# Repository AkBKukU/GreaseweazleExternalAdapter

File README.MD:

# Greaseweazle External Floppy Adapter

This is a simple PCB design that directly adapts a Greaseweazle floppy interface to a 25 pin (or 37 pin) external floppy drive. The idea was to allow the use of cheap external floppy drives that are missing their pass through hardware card that makes them usable in a vintage system. With the adapter you get an easy to use and robustly  cased floppy drive for use with disk image hardware.  
  
## Assembly  
Take note that the DB25 connector is put on the opposite side of the board than the power and 34 pin IDC connectors. The trace routing would have needed to be flipped to keep them all on top and this was made in a bit of a rush. It would be possible to re-route the PCB to have the connector on top, but all traces would have to cross making the routing much more complicated.

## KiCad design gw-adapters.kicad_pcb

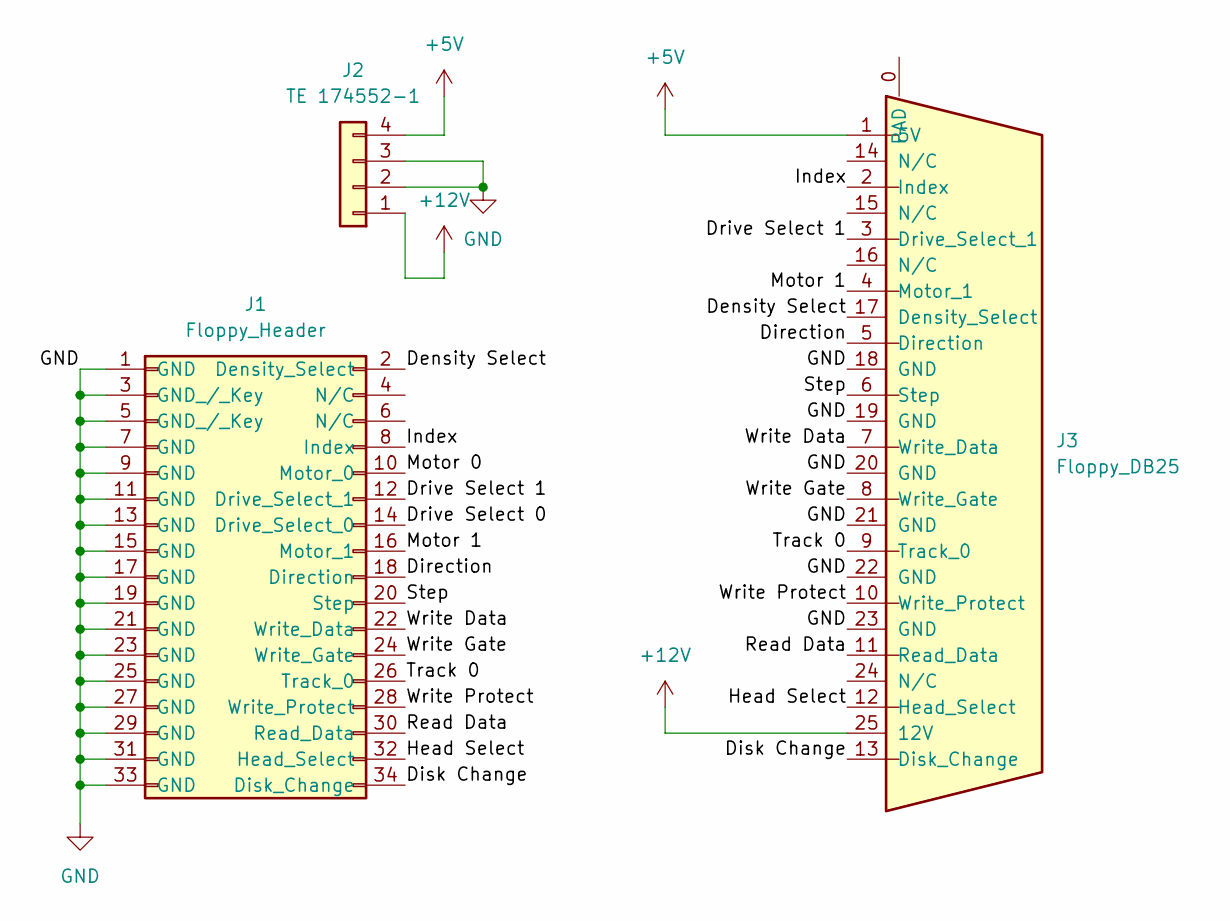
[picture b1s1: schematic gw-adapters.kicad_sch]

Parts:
J1: Floppy_Header; PinSocket_2x17_P2.54mm_Horizontal
J2: TE 174552-1; 1745521
J3: Floppy_DB25; DSUB-25_Male_Horizontal_P2.77x2.84mm_EdgePinOffset4.94mm_Ho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

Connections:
+5V: J2.4, J3.1 (5V)
+12V: J2.1, J3.25 (12V)
/Density Select: J1.2 (Density_Select), J3.17 (Density_Select)
/Direction: J1.18 (Direction), J3.5 (Direction)
/Disk Change: J1.34 (Disk_Change), J3.13 (Disk_Change)
/Drive Select 0: J1.14 (Drive_Select_0)
/Drive Select 1: J1.12 (Drive_Select_1), J3.3 (Drive_Select_1)
/Head Select: J1.32 (Head_Select), J3.12 (Head_Select)
/Index: J1.8 (Index), J3.2 (Index)
/Motor 0: J1.10 (Motor_0)
/Motor 1: J1.16 (Motor_1), J3.4 (Motor_1)
/Read Data: J1.30 (Read_Data), J3.11 (Read_Data)
/Step: J1.20 (Step), J3.6 (Step)
/Track 0: J1.26 (Track_0), J3.9 (Track_0)
/Write Data: J1.22 (Write_Data), J3.7 (Write_Data)
/Write Gate: J1.24 (Write_Gate), J3.8 (Write_Gate)
/Write Protect: J1.28 (Write_Protect), J3.10 (Write_Protect)
GND: J1.1 (GND), J1.3 (GND_/_Key), J1.5 (GND_/_Key), J1.7 (GND), J1.9 (GND), J1.11 (GND), J1.13 (GND), J1.15 (GND), J1.17 (GND), J1.19 (GND), J1.21 (GND), J1.23 (GND), J1.25 (GND), J1.27 (GND), J1.29 (GND), J1.31 (GND), J1.33 (GND), J2.2, J2.3, J3.18 (GND), J3.19 (GND), J3.20 (GND), J3.21 (GND), J3.22 (GND), J3.23 (GND)

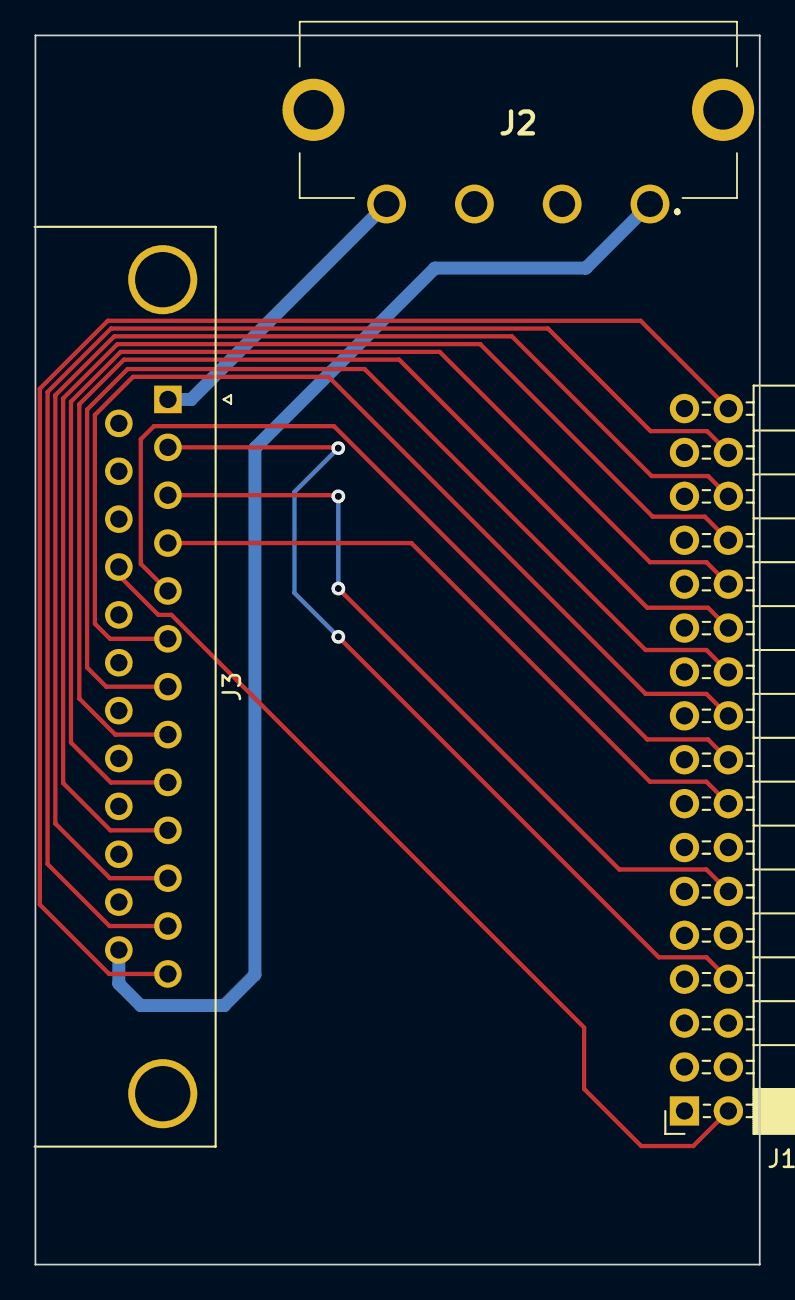
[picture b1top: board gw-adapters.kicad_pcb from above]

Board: 2 copper layers, 41.9 x 71.1 mm, 3 parts (0 on the bottom side), 16 nets.

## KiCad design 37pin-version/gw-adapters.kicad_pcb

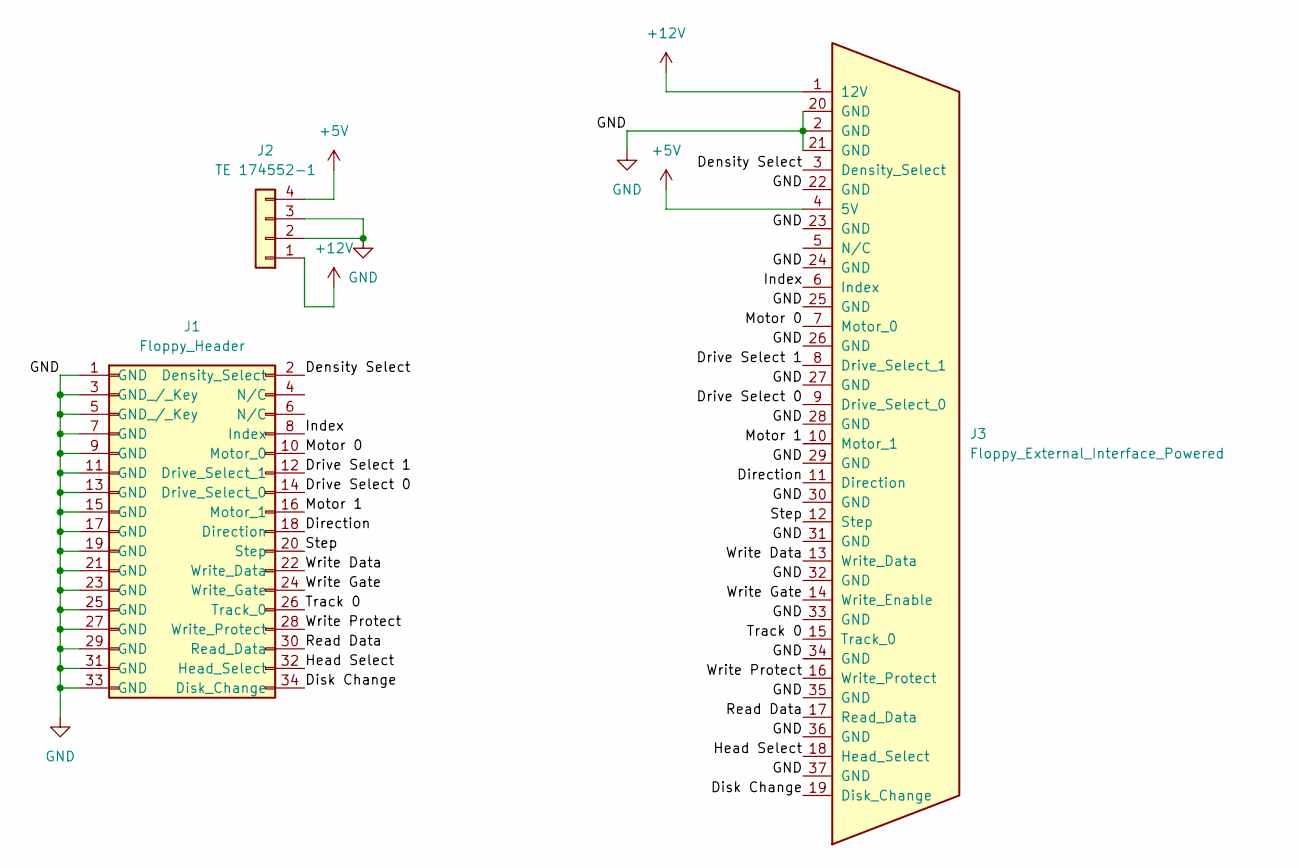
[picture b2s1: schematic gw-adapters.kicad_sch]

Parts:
J1: Floppy_Header; PinSocket_2x17_P2.54mm_Horizontal
J2: TE 174552-1; 1745521
J3: Floppy_External_Interface_Powered; DSUB-37_Female_Horizontal_P2.77x2.84mm_EdgePinOffset4.94mm_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

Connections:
+5V: J2.4, J3.4 (5V)
+12V: J2.1, J3.1 (12V)
/Density Select: J1.2 (Density_Select), J3.3 (Density_Select)
/Direction: J1.18 (Direction), J3.11 (Direction)
/Disk Change: J1.34 (Disk_Change), J3.19 (Disk_Change)
/Drive Select 0: J1.14 (Drive_Select_0), J3.9 (Drive_Select_0)
/Drive Select 1: J1.12 (Drive_Select_1), J3.8 (Drive_Select_1)
/Head Select: J1.32 (Head_Select), J3.18 (Head_Select)
/Index: J1.8 (Index), J3.6 (Index)
/Motor 0: J1.10 (Motor_0), J3.7 (Motor_0)
/Motor 1: J1.16 (Motor_1), J3.10 (Motor_1)
/Read Data: J1.30 (Read_Data), J3.17 (Read_Data)
/Step: J1.20 (Step), J3.12 (Step)
/Track 0: J1.26 (Track_0), J3.15 (Track_0)
/Write Data: J1.22 (Write_Data), J3.13 (Write_Data)
/Write Gate: J1.24 (Write_Gate), J3.14 (Write_Enable)
/Write Protect: J1.28 (Write_Protect), J3.16 (Write_Protect)
GND: J1.1 (GND), J1.3 (GND_/_Key), J1.5 (GND_/_Key), J1.7 (GND), J1.9 (GND), J1.11 (GND), J1.13 (GND), J1.15 (GND), J1.17 (GND), J1.19 (GND), J1.21 (GND), J1.23 (GND), J1.25 (GND), J1.27 (GND), J1.29 (GND), J1.31 (GND), J1.33 (GND), J2.2, J2.3, J3.2 (GND), J3.20 (GND), J3.21 (GND), J3.22 (GND), J3.23 (GND), J3.24 (GND), J3.25 (GND), J3.26 (GND), J3.27 (GND), J3.28 (GND), J3.29 (GND), J3.30 (GND), J3.31 (GND), J3.32 (GND), J3.33 (GND), J3.34 (GND), J3.35 (GND), J3.36 (GND), J3.37 (GND)

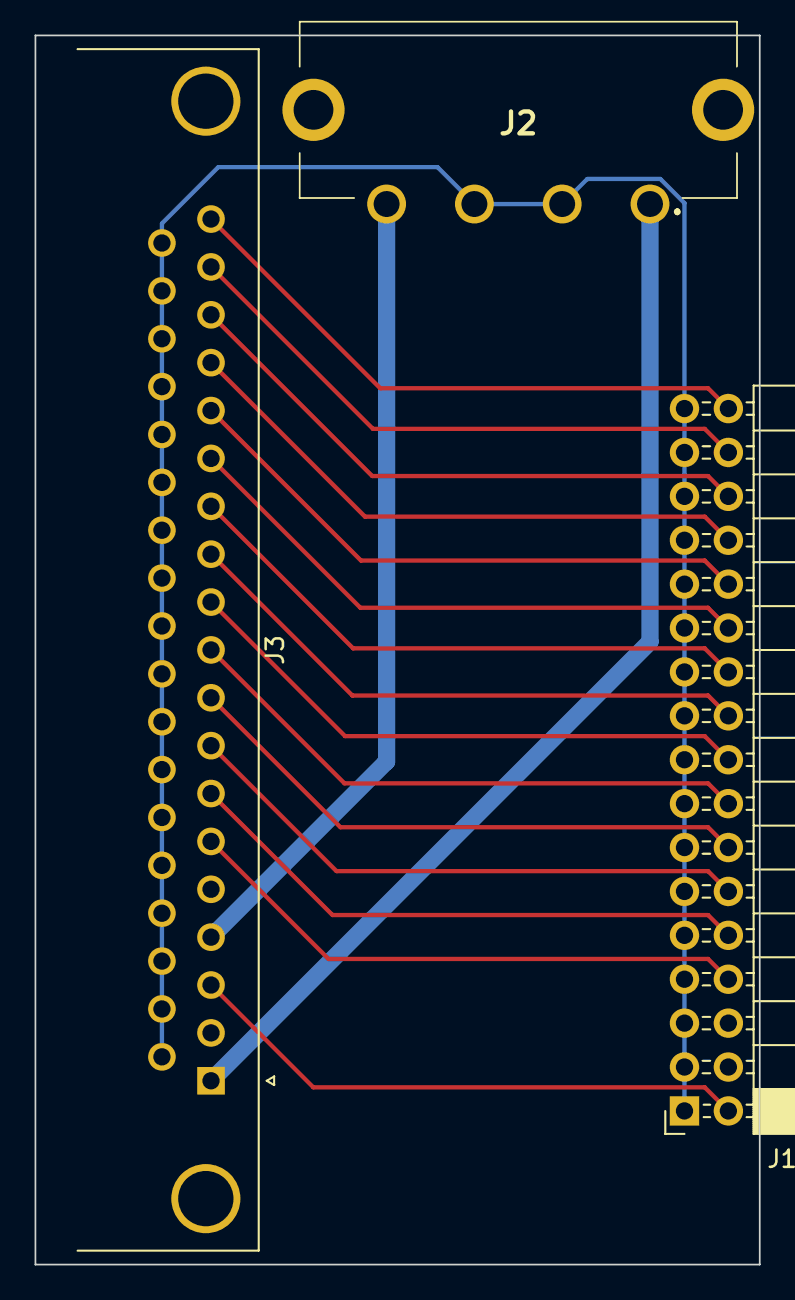
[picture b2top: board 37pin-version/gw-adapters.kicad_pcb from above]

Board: 2 copper layers, 41.9 x 71.1 mm, 3 parts (0 on the bottom side), 18 nets.

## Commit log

2023-05-24 Init repot
2023-05-28 Rerouted
    Rerouted traces to allow for all components to be placed on the top of the board.
